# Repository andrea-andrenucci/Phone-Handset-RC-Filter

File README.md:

# Phone Handset RC Filter

*I apologise profusely for the inability to make a simple, simmetric photo*
<br></br>

This project is mainly inspired by the works of [Ryan Mobitz](https://www.production-expert.com/production-expert-1/use-an-old-phone-handset-to-produce-a-lo-fi-mic) and [Noisegate](https://noisegate.com.au/how-to-create-a-stereo-microphone-from-an-old-telephone-handset/).

The main contribution of this project is treating the telephone handset as a separate module from the main circuit, which is designed as an independent audio effect stage.

Another major difference is the use of an external power supply. This allows the use of a carbon microphone even without a mixer providing phantom power.  
Thanks to the lower supply voltage (9V instead of the standard 48V phantom power), there is no need for an impedance-matching transformer, significantly reducing manufacturing costs and complexity.

``` Python
The project contains:
    ./imgs/ # All the figures used in the README
    ./schema_and_pcb/ #This contains the main source files
        |
        |-> ./out/ #Files for JLC PCB
        |
        |-> ... # All the kicad files
        |
        |-> ./Case.zip/ #Contains al the .stl for the enclosure
```
More technical info and measurements about the microphone can be found in [MEASUREMENTS](./MEASUREMENTS.md)

## Overview

The circuit is a simple RC-based filter and conditioning stage designed to work with vintage telephone handsets, supporting both the dynamic capsule and the carbon microphone.

The reference in the schematic is an headset from an italian Siemens S62 (aka Bigrigio):

- **Dynamic capsule (≈55 Ω)**
- **Carbon microphone (≈100 kΩ)**

A switch allows selecting the appropriate signal path depending on the capsule type.

The output is provided via a standard **XLR3 panel connector**, making the device compatible with mixers, audio interfaces, and recording systems.

Power is supplied externally through a **9V DC input (center negative)**, the standard de facto for effects.

---

## Electrical Schematic
<center>
    
</center>
<br></br>

Both the schematic and the PCB were designed using **KiCad**.

The circuit can be divided into four main sections:

### 1. Input Section (Handset Connector)
The handset is connected via a 3-pin terminal block:

- Pin 1: Carbon Microphone
- Pin 2: Dynamic Capsule
- Pin 3: Common Ground

<center>
    
</center>

<br></br>

#### Dynamic Capsule Characteristics

- Very low impedance (~55 Ω)
- Does **not** require bias voltage
- Generates signal directly from diaphragm movement

#### Carbon Microphone Characteristics

- High impedance (~100 kΩ)
- Requires **DC bias current**
- Output is a resistance variation modulating the bias voltage
- Produces strong midrange distortion (classic telephone sound)

Because the two technologies behave completely differently, they require different conditioning paths.

### 2. RC Filter Network
The **R1 (33kΩ)** provides **bias current limiting** for the carbon microphone when in carbon mode. R1:
- Limits current from the 9V supply
- Sets operating point of the carbon capsule
- Prevents excessive noise and overheating

Typical carbon microphones work best with a few milliamps of current.  
33kΩ at 9V provides a safe, low-current bias suitable for vintage elements.

The pair **R2 (33kΩ), C2(10µF)** forms a **high-pass RC filter**.

This network shapes the frequency response, emphasizing the lo-fi telephone character by limiting bandwidth and controlling gain.
The **R3 (50kΩ on the schematic, a 47kΩ was actually used)** resistor acts as a level control.

<center>
    
</center>
<br></br>

**R4 (10kΩ) and C1 (1µF)** work in a similiar fashon, acting as a filter for the dynamic capsule.

This contributes slightly to the “telephone effect”, although the main bandwidth limitation comes from the capsule itself.

### 3. Power and Output Stage

- **9V DC input (center negative)**
- **LED + 750Ω resistor** for power indication
- **XLR3 output connector**

The XLR pinout follows the standard convention:

- Pin 1: Signal -
- Pin 2: Signal +

A **DPDT push switch** allows selecting the correct configuration depending on the capsule type:

- Dynamic mode
- Carbon mode (powered)

This isolates the microphone from the power section when not needed.

<center>
    
</center>
<br></br>

> Note:  
> This is **not a fully balanced active output**.  
> It is pseudo-balanced/passive and works well for short cable runs.
>
> For professional long runs, an active balanced driver could be added.

---

## PCB

The PCB was designed in KiCad with through-hole components for easy assembly and repair.

Design goals:

- Compact footprint
- Simple routing
- Clear separation between power and signal paths
- Easy integration into a custom enclosure

In order to connect both the DPDT and the XLR i used a **JST** standard 2mm terminal

<center>
    
</center>

---

## Enclosure

The enclosure was designed in CAD (Onshape) and consists of:

- Base plate
- Main body
- Top plate

The layout ensures mechanical stability and easy access to all connectors.

<center>
    
</center>

<center>
    
</center>

<center>
    
</center>

<center>
    
</center>

---

## Future Improvements and Considerations

This project started as an experiment and as a way to understand better how simple analog circuits behave in the real world.

It was the first time I designed a complete audio stage from scratch and along the way I definitely made a few mistakes. For example, the value of the **R3 resistor** was tuned empirically after testing with a potentiometer, and only later replaced with the closest fixed value I had available. In hindsight, using a 100kΩ trimmer from the beginning would have made the tuning process much cleaner and more flexible.

I also chose a female XLR panel connector, which is not the standard choice for this kind of device. A male XLR would have been more appropriate, but I worked with what I could source locally at the time.

Despite these imperfections, the device works reliably and captures exactly the grittyness telephone sound.

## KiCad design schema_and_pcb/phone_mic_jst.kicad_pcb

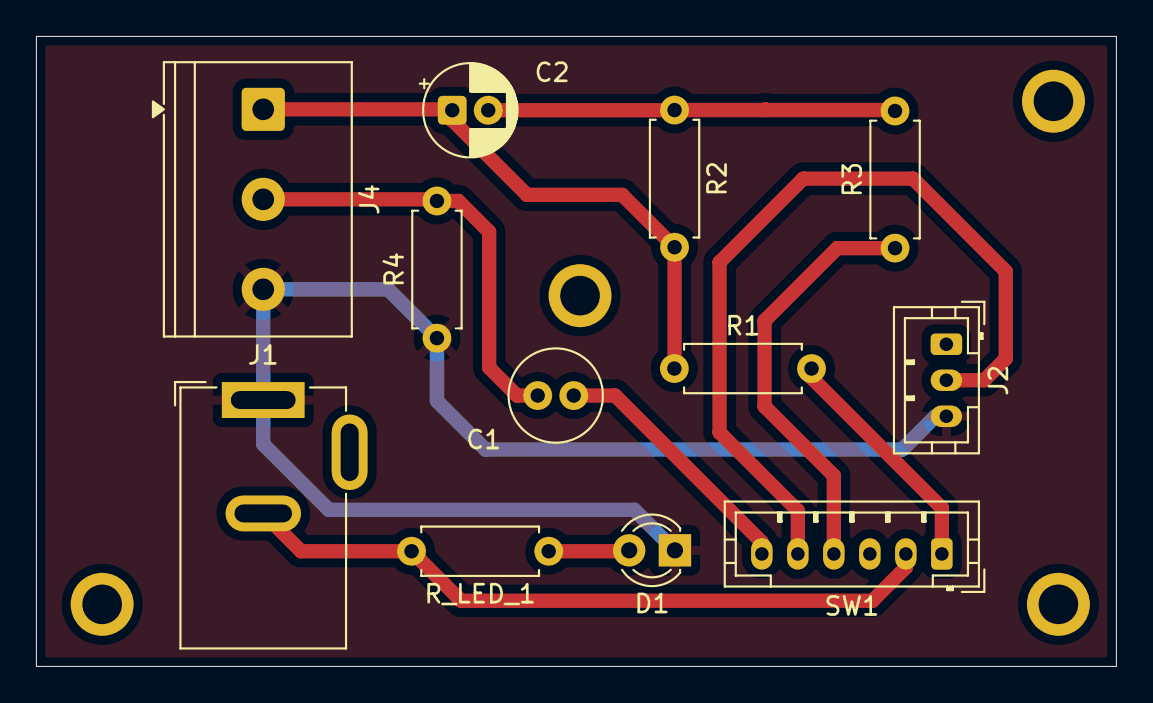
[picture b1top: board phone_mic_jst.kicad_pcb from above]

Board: 2 copper layers, 60.0 x 35.0 mm, 12 parts (0 on the bottom side), 10 nets.

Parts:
C1: 1uF; C_Radial_D5.0mm_H11.0mm_P2.00mm
C2: 10 uF; CP_Radial_D5.0mm_P2.00mm
D1: LED; LED_D3.0mm
J1: Coaxial_Power - center negative; BarrelJack_GCT_DCJ200-10-A_Horizontal
J2: XLR3; JST_PH_B3B-PH-K_1x03_P2.00mm_Vertical
J4: N/D/C; TerminalBlock_Philmore_TB133_1x03_P5.00mm_Horizontal
R1, R2: 33k; R_Axial_DIN0207_L6.3mm_D2.5mm_P7.62mm_Horizontal
R3: 41k; R_Axial_DIN0207_L6.3mm_D2.5mm_P7.62mm_Horizontal
R4: 10k; R_Axial_DIN0207_L6.3mm_D2.5mm_P7.62mm_Horizontal
R_LED_1: 1.7 k; R_Axial_DIN0207_L6.3mm_D2.5mm_P7.62mm_Horizontal
SW1: SW_Push_DPDT; JST_PH_B6B-PH-K_1x06_P2.00mm_Vertical

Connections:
+9V: J1.2 (Ext), R_LED_1.2, SW1.2 (B)
GND: D1.1 (K), J1.1 (In), J2.3, J4.3, R4.1
unnamed: C1.2, SW1.6 (C)
unnamed: C2.2, R2.1, R3.2
unnamed: D1.2 (A), R_LED_1.1
unnamed: J2.2, SW1.5 (B)
unnamed: C2.1, J4.1, R1.1, R2.2
unnamed: C1.1, J4.2, R4.2
unnamed: R1.2, SW1.1 (A)
unnamed: R3.1, SW1.4 (A)

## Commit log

2026-02-14 Added measurements
